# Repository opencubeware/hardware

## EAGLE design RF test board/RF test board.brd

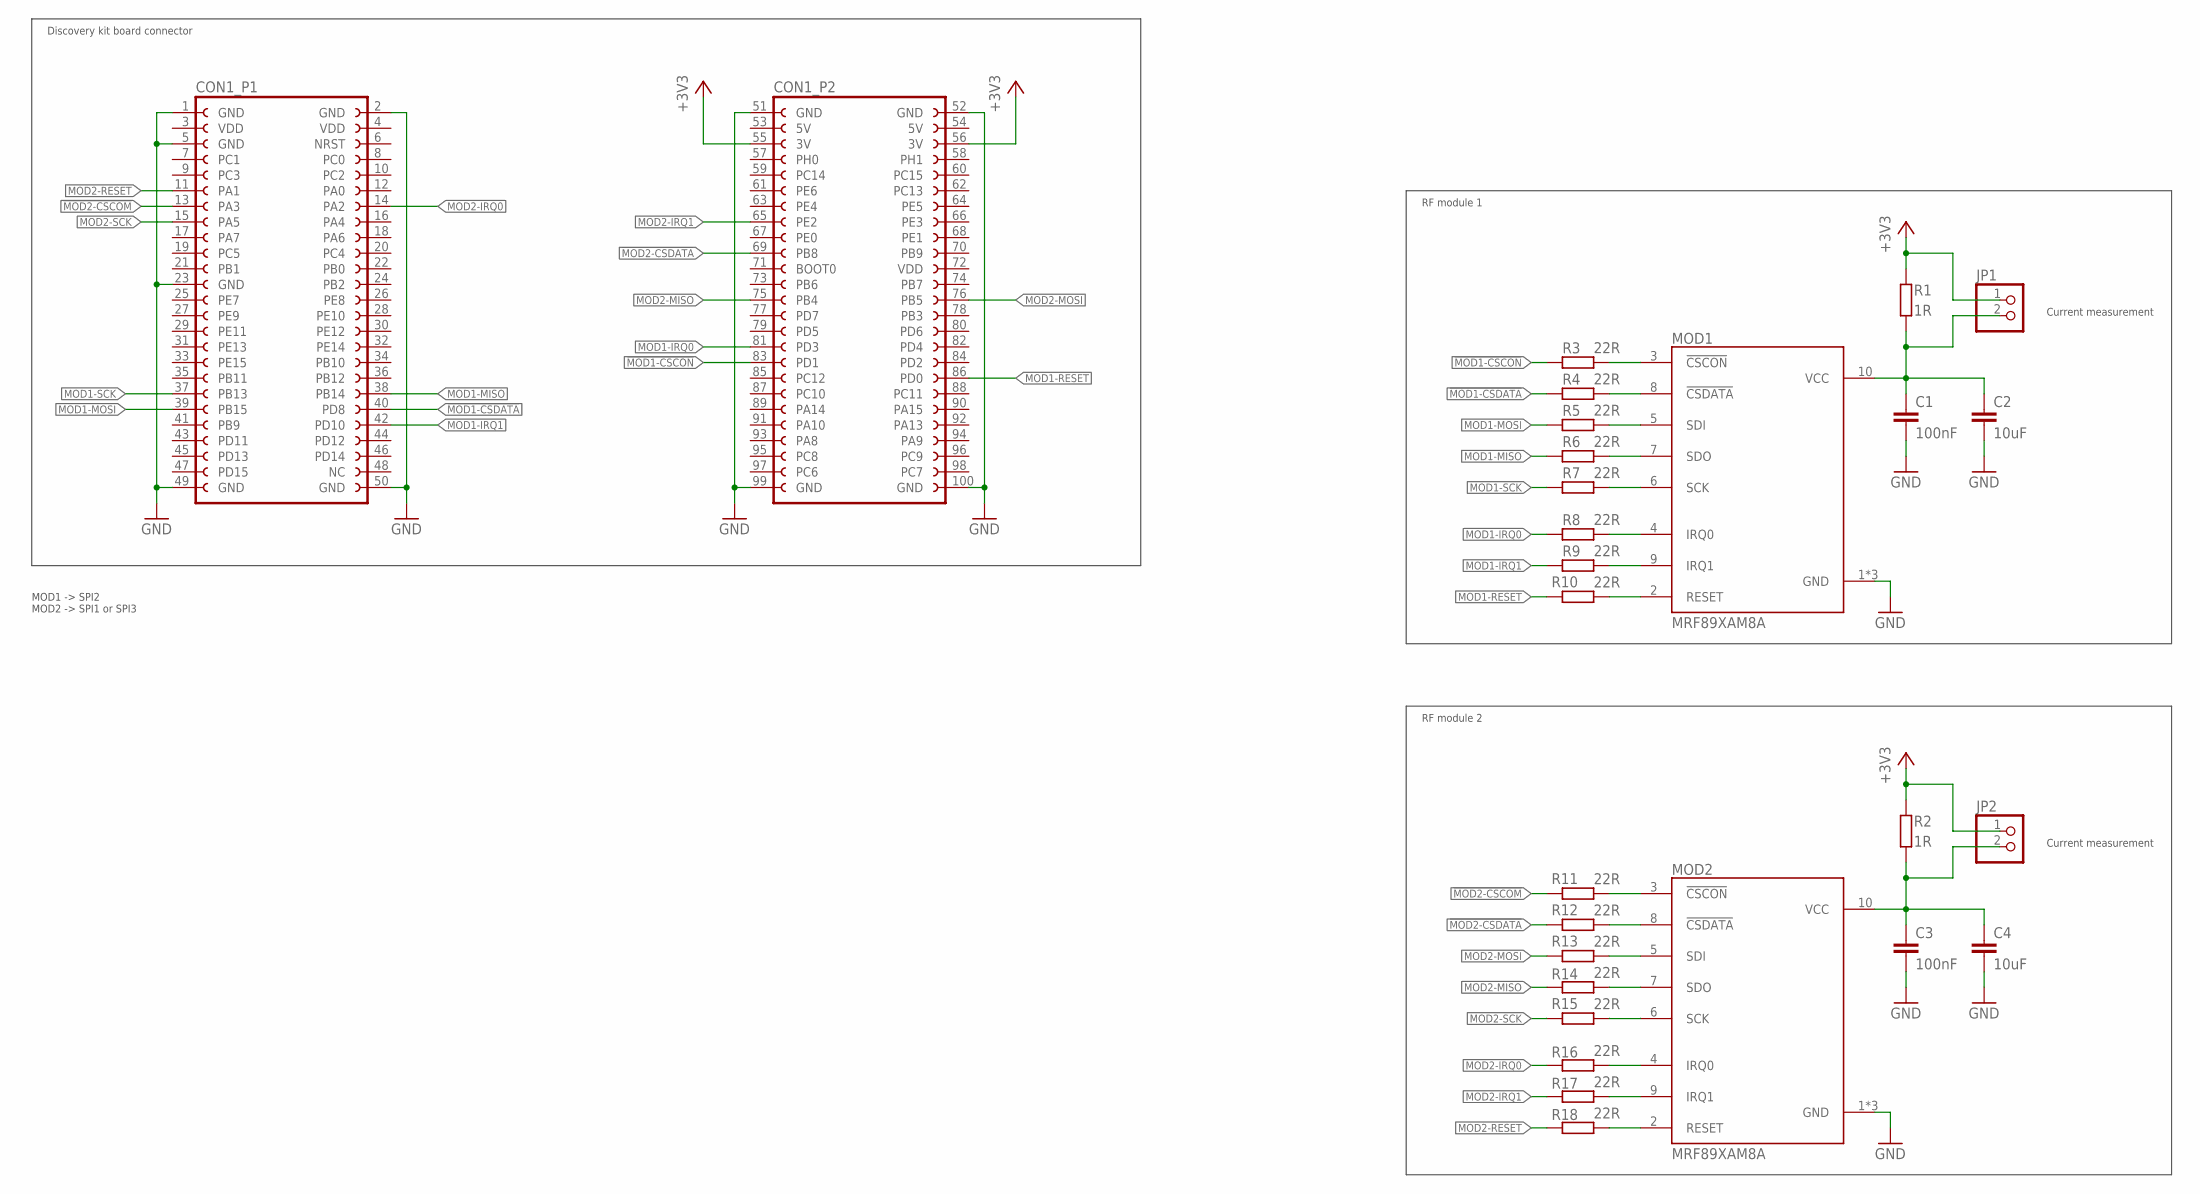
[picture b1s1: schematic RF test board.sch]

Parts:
C1, C3: 100nF; C0603K
C2, C4: 10uF; C1206K
CON1: STM32F4DISCOVERY-CONNECTOR; STM32F4DISCOVERY_CONNECTOR
JP1, JP2: PINHD-1X2; 1X02
MOD1, MOD2: MRF89XAM8A
R1, R2: 1R; R0603
R3, R4, R5, R6, R7, R8, R9, R10, R11, R12, R13, R14, R15, R16, R17, R18: 22R; R0603

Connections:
!MOD1-CSCON: CON1.83 (PD1), R3.2
!MOD1-CSDATA: CON1.40 (PD8), R4.2
!MOD2-CSCOM: CON1.13 (PA3), R11.2
!MOD2-CSDATA: CON1.69 (PB8), R12.2
+3V3: CON1.55 (3V), CON1.56 (3V), JP1.1, JP2.1, R1.2, R2.2
GND: C1.2, C2.2, C3.2, C4.2, CON1.1 (GND), CON1.2 (GND), CON1.5 (GND), CON1.23 (GND), CON1.49 (GND), CON1.50 (GND), CON1.51 (GND), CON1.52 (GND), CON1.99 (GND), CON1.100 (GND), MOD1.1 (GND), MOD1.11 (GND), MOD1.12 (GND), MOD2.1 (GND), MOD2.11 (GND), MOD2.12 (GND)
MOD1-IRQ0: CON1.81 (PD3), R8.2
MOD1-IRQ1: CON1.42 (PD10), R9.2
MOD1-MISO: CON1.38 (PB14), R6.2
MOD1-MOSI: CON1.39 (PB15), R5.2
MOD1-RESET: CON1.86 (PD0), R10.2
MOD1-SCK: CON1.37 (PB13), R7.2
MOD2-IRQ0: CON1.14 (PA2), R16.2
MOD2-IRQ1: CON1.65 (PE2), R17.2
MOD2-MISO: CON1.75 (PB4), R14.2
MOD2-MOSI: CON1.76 (PB5), R13.2
MOD2-RESET: CON1.11 (PA1), R18.2
MOD2-SCK: CON1.15 (PA5), R15.2
unnamed: C1.1, C2.1, JP1.2, MOD1.10 (VCC), R1.1
unnamed: C3.1, C4.1, JP2.2, MOD2.10 (VCC), R2.1
unnamed: MOD1.3 (!CSCON), R3.1
unnamed: MOD1.8 (!CSDATA), R4.1
unnamed: MOD1.5 (SDI), R5.1
unnamed: MOD1.7 (SDO), R6.1
unnamed: MOD1.6 (SCK), R7.1
unnamed: MOD1.4 (IRQ0), R8.1
unnamed: MOD1.9 (IRQ1), R9.1
unnamed: MOD1.2 (RESET), R10.1
unnamed: MOD2.3 (!CSCON), R11.1
unnamed: MOD2.8 (!CSDATA), R12.1
unnamed: MOD2.5 (SDI), R13.1
unnamed: MOD2.7 (SDO), R14.1
unnamed: MOD2.6 (SCK), R15.1
unnamed: MOD2.4 (IRQ0), R16.1
unnamed: MOD2.9 (IRQ1), R17.1
unnamed: MOD2.2 (RESET), R18.1

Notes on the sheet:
Discovery kit board connector
RF module 1
Current measurement
RF module 2
MOD1 -> SPI2 MOD2 -> SPI1 or SPI3

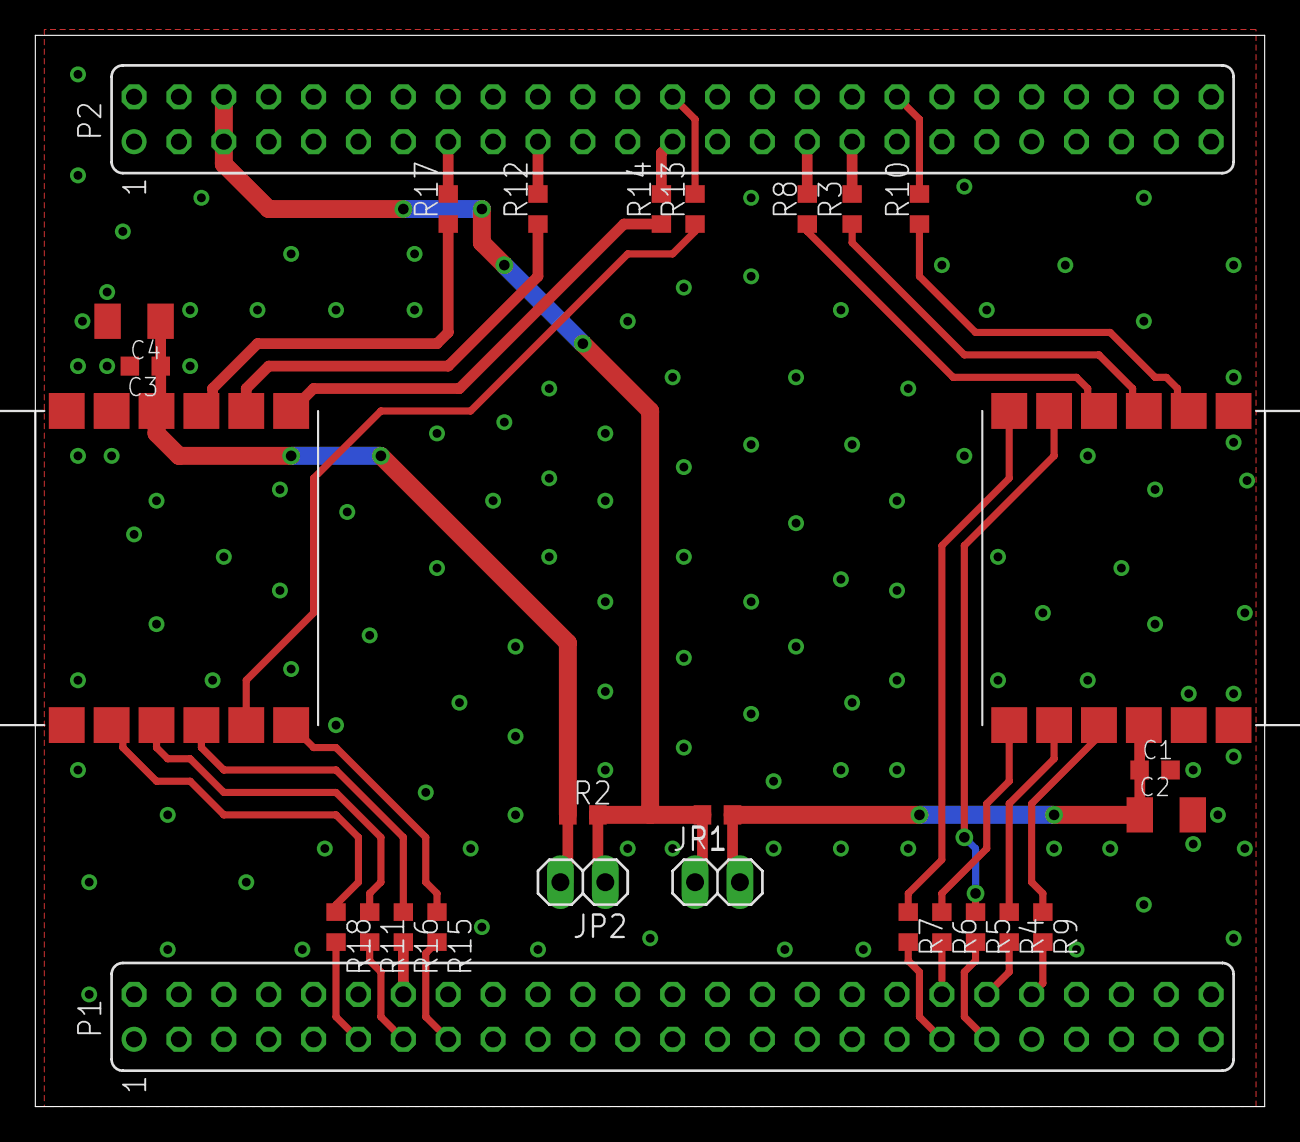
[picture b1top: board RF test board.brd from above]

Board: 2 copper layers, 69.6 x 60.6 mm, 27 parts (0 on the bottom side), 36 nets.

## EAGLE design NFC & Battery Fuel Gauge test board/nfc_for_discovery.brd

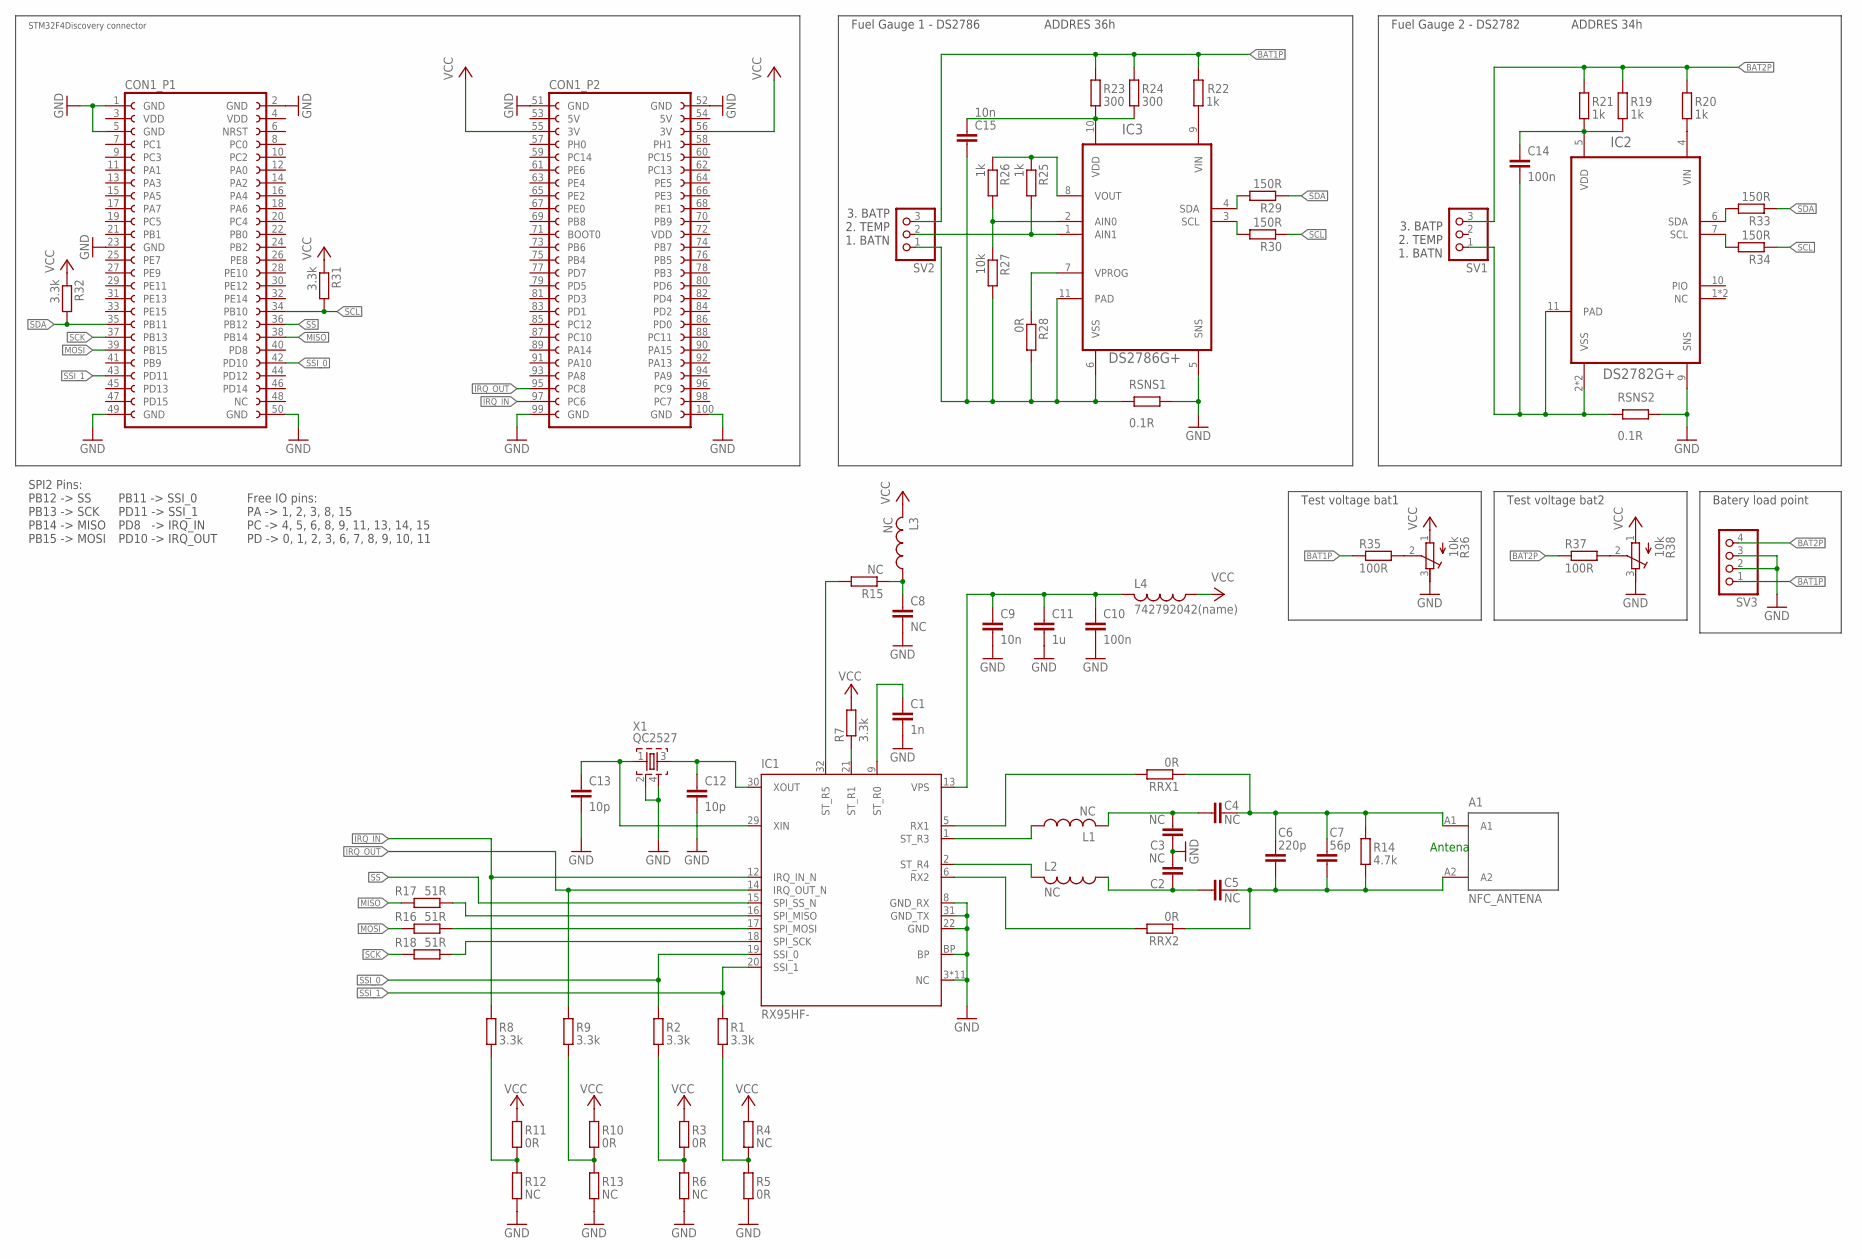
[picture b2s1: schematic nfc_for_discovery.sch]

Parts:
A1: NFC_ANTENA
C1: 1n; C0603
C2, C3, C4, C5, C8: NC; C0603
C6: 220p; C0603
C7: 56p; C0603
C9, C15: 10n; C0603
C10, C14: 100n; C0603
C11: 1u; C0603K
C12, C13: 10p; C0603
CON1: STM32F4DISCOVERY-CONNECTOR; STM32F4DISCOVERY_CONNECTOR
IC1: RX95HF-; VFQFPN32
IC2: DS2782G+; DFN300X400
IC3: DS2786G+; DFN300X300X80-11N
L1, L2, L3: NC; L2012C
L4: 742792042(name); L2012C
R1, R2, R7, R8, R9, R31, R32: 3.3k; R0603
R3, R5, R10, R11, R28: 0R; R0603
R4, R6, R12, R13, R15: NC; R0603
R14: 4.7k; R0603
R16, R17, R18: 51R; R0603
R19, R20, R21, R22, R25, R26: 1k; R0603
R23, R24: 300; R0603
R27: 10k; R0603
R29, R30, R33, R34: 150R; R0603
R35, R37: 100R; R0603
R36, R38: 10k; RTRIM4G/J
RRX1, RRX2: 0R; R0603
RSNS1, RSNS2: 0.1R; R0603
SV1, SV2: PINHD-1X3/90; 1X03/90
SV3: PINHD-1X4/90; 1X04/90
X1: QC2527

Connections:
BAT1N: C15.2, IC3.6 (VSS), IC3.11 (PAD), R27.2, R28.2, RSNS1.2, SV2.1
BAT1P: R22.1, R23.1, R24.1, R35.1, SV2.3, SV3.1
BAT2N: C14.2, IC2.2 (VSS), IC2.3 (VSS), IC2.11 (PAD), RSNS2.2, SV1.1
BAT2P: R19.1, R20.1, R21.1, R37.1, SV1.3, SV3.4
GND: C1.1, C2.2, C3.1, C8.2, C9.2, C10.2, C11.2, C12.2, C13.2, CON1.1 (GND), CON1.2 (GND), CON1.5 (GND), CON1.23 (GND), CON1.49 (GND), CON1.50 (GND), CON1.51 (GND), CON1.52 (GND), CON1.99 (GND), CON1.100 (GND), IC1.3 (NC), IC1.4 (NC), IC1.7 (NC), IC1.8 (GND_RX), IC1.10 (NC), IC1.11 (NC), IC1.22 (GND), IC1.23 (NC), IC1.24 (NC), IC1.25 (NC), IC1.26 (NC), IC1.27 (NC), IC1.28 (NC), IC1.31 (GND_TX), IC1.BP, IC2.9 (SNS), IC3.5 (SNS), R5.1, R6.1, R12.1, R13.1, R36.3 (E), R38.3 (E), RSNS1.1, RSNS2.1, SV3.2, SV3.3, X1.2, X1.4
IRQ_IN: CON1.97 (PC6), IC1.12 (IRQ_IN_N), R8.2
IRQ_OUT: CON1.95 (PC8), IC1.14 (IRQ_OUT_N), R9.2
MISO: CON1.38 (PB14), R17.2
MOSI: CON1.39 (PB15), R16.2
unnamed: C14.1, IC2.5 (VDD), R19.2, R21.2
unnamed: IC1.16 (SPI_MISO), R17.1
unnamed: IC1.17 (SPI_MOSI), R16.1
unnamed: IC1.18 (SPI_SCK), R18.1
unnamed: IC2.4 (VIN), R20.2
unnamed: IC3.4 (SDA), R29.2
unnamed: IC3.3 (SCL), R30.2
unnamed: R1.1, R4.1, R5.2
unnamed: R2.1, R3.1, R6.2
unnamed: C2.1, C5.2, L2.1
unnamed: IC1.21 (ST_R1), R7.1
unnamed: C1.2, IC1.9 (ST_R0)
unnamed: R8.1, R11.1, R12.2
unnamed: R9.1, R10.1, R13.2
unnamed: C3.2, C4.2, L1.2
unnamed: A1.A1, C4.1, C6.2, C7.2, R14.1, RRX1.1
unnamed: A1.A2, C5.1, C6.1, C7.1, R14.2, RRX2.1
unnamed: IC1.6 (RX2), RRX2.2
unnamed: IC1.5 (RX1), RRX1.2
unnamed: IC1.1 (ST_R3), L1.1
unnamed: IC1.2 (ST_R4), L2.2
unnamed: IC1.32 (ST_R5), R15.2
unnamed: C8.1, L3.1, R15.1
unnamed: C9.1, C10.1, C11.1, IC1.13 (VPS), L4.2
unnamed: IC3.9 (VIN), R22.2
unnamed: C12.1, IC1.30 (XOUT), X1.3
unnamed: C13.1, IC1.29 (XIN), X1.1
unnamed: C15.1, IC3.10 (VDD), R23.2, R24.2
unnamed: IC2.6 (SDA), R33.2
unnamed: IC2.7 (SCL), R34.2
unnamed: IC3.2 (AIN0), R26.2, R27.1
unnamed: IC3.1 (AIN1), R25.2, SV2.2
unnamed: IC3.8 (VOUT), R25.1, R26.1
unnamed: IC3.7 (VPROG), R28.1
unnamed: R35.2, R36.2 (S)
unnamed: R37.2, R38.2 (S)
SCK: CON1.37 (PB13), R18.2
SCL: CON1.34 (PB10), R30.1, R31.2, R34.1
SDA: CON1.35 (PB11), R29.1, R32.2, R33.1
SS: CON1.36 (PB12), IC1.15 (SPI_SS_N)
SSI_0: CON1.42 (PD10), IC1.19 (SSI_0), R2.2
SSI_1: CON1.43 (PD11), IC1.20 (SSI_1), R1.2
VCC: CON1.55 (3V), CON1.56 (3V), L3.2, L4.1, R3.2, R4.2, R7.2, R10.2, R11.2, R31.1, R32.1, R36.1 (A), R38.1 (A)

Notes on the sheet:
Antena
SPI2 Pins: PB12 -> SS PB13 -> SCK PB14 -> MISO PB15 -> MOSI
STM32F4Discovery connector
PB11 -> SSI_0 PD11 -> SSI_1 PD8 -> IRQ_IN PD10 -> IRQ_OUT
Free IO pins: PA -> 1, 2, 3, 8, 15 PC -> 4, 5, 6, 8, 9, 11, 13, 14, 15 PD -> 0, 1, 2, 3, 6, 7, 8, 9, 10, 11
3. BATP 2. TEMP 1. BATN
Fuel Gauge 1 - DS2786
Fuel Gauge 2 - DS2782
Batery load point
ADDRES 36h
ADDRES 34h
Test voltage bat1
Test voltage bat2

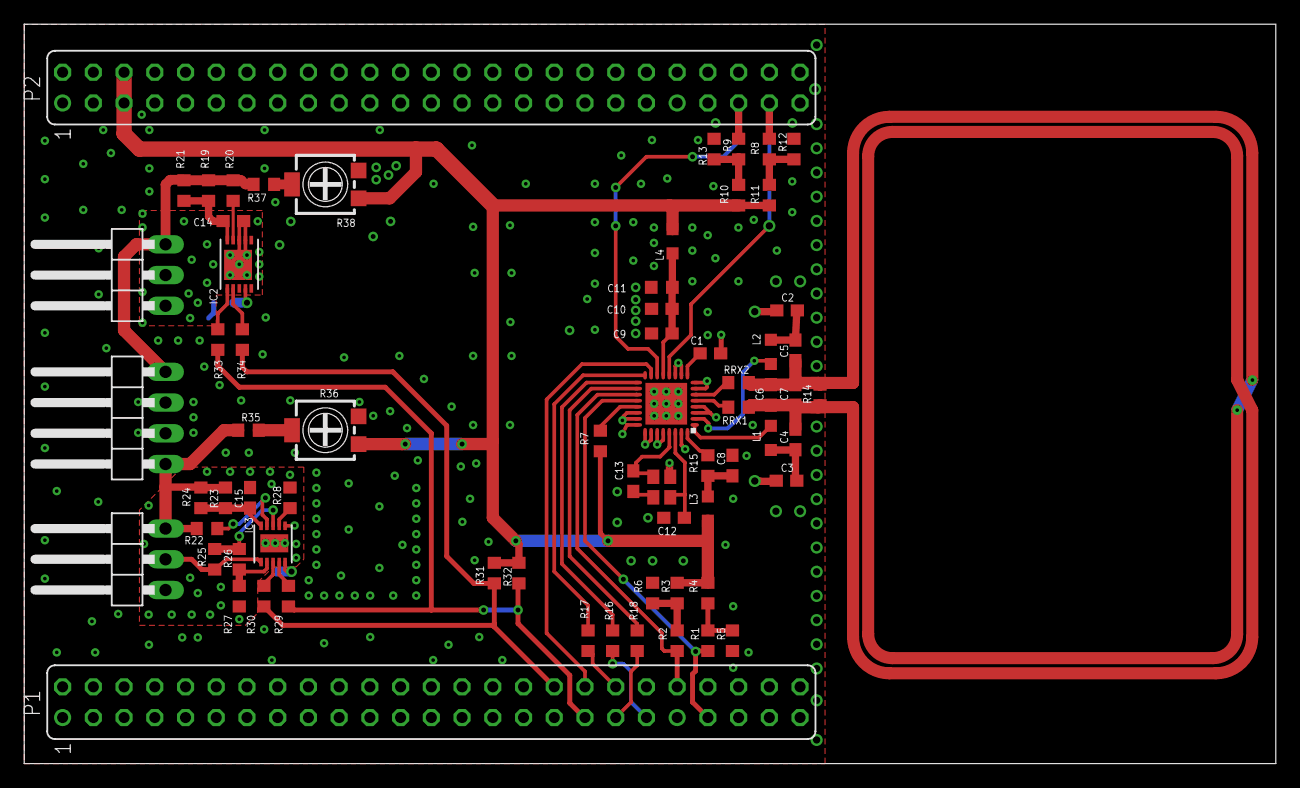
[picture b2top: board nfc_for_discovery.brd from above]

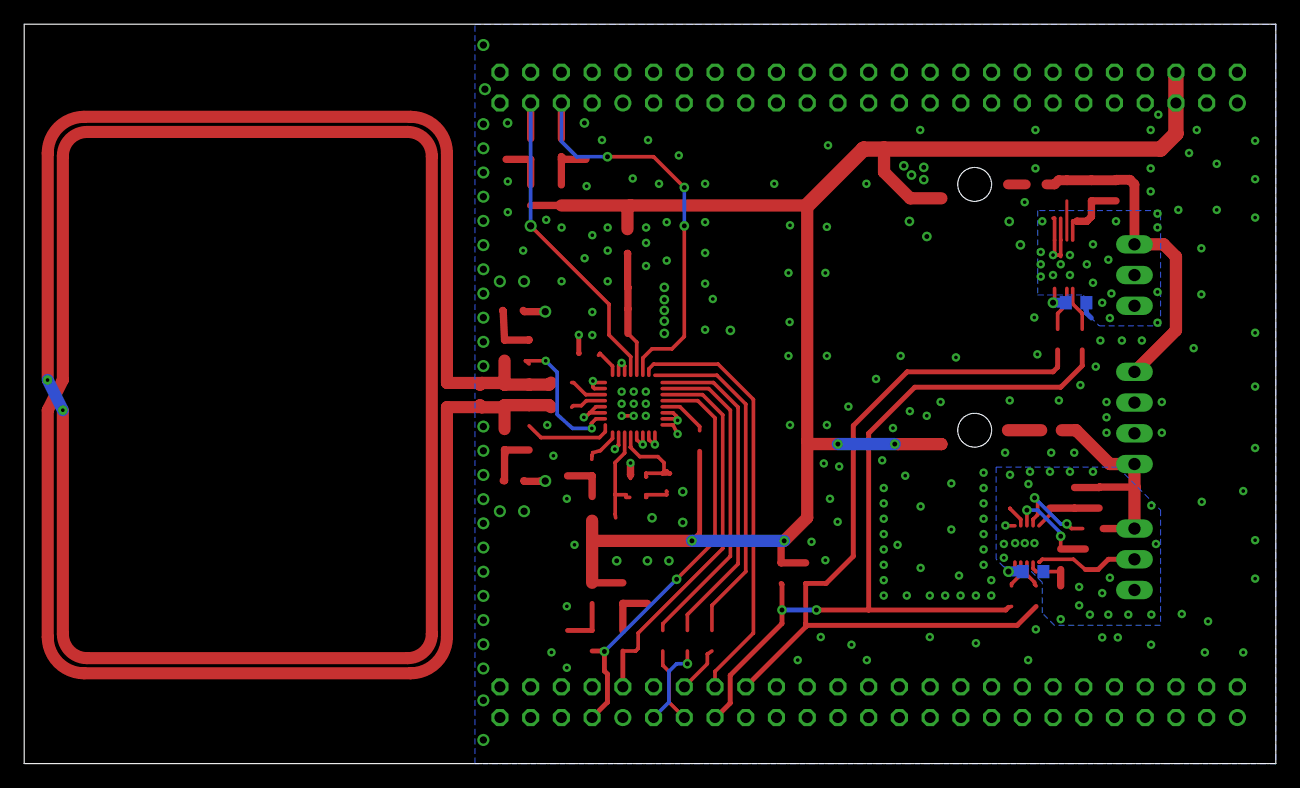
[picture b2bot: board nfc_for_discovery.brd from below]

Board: 2 copper layers, 103.5 x 61.1 mm, 70 parts (3 on the bottom side), 52 nets.

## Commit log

2015-05-04 added NFC test board with gerber files
2015-06-16 BQ27510.lbr
    Eagle library for BQ27510
2015-06-16 Create stm32f4Discovery_connector.lbr
    Made by Paweł Okas
2015-06-21 added folder for LCD test board
2015-07-08 dodano zlacza do stackmaty i wyswietlacza
2015-07-08 dodano biblioteke przetwornicy
2015-07-10 polaczono piny od lcd
2015-07-11 polaczono wyswietlacz i stackmate do portu usart procesora, dodano invertery
2015-07-12 dodano kondensatory przy złączu lcd
2015-07-14 added RF module test board, added MRF89XAM8A library
2015-07-15 dodano obrys wyświetlacza do biblioteki
2015-07-25 Dodano pojemnościowy kontroler panelu dotykowego
2015-07-25 added resistive touch panel controller
2015-07-25 added touch panel connectors
2015-07-25 improved schematic readability
